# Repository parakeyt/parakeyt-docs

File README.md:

# parakeyt-docs
documentation and testing for parakeyt

# structure

## `reference-design/`
contains a completed reference design to act as a testing platform and schematic example of a potential parakeyt board.

it is hand designed, placed, and routed. it is not an actual output of the parakeyt toolchain.

# attribution
Footprints, models, symbols:
- RP2040-zero from https://github.com/crides/kleeb/ (MIT License)
- TLC59108IRGYR from manufacturer
- TLA2528IRTER from manufacturer
- AH49FNTR-G1 from manufacturer

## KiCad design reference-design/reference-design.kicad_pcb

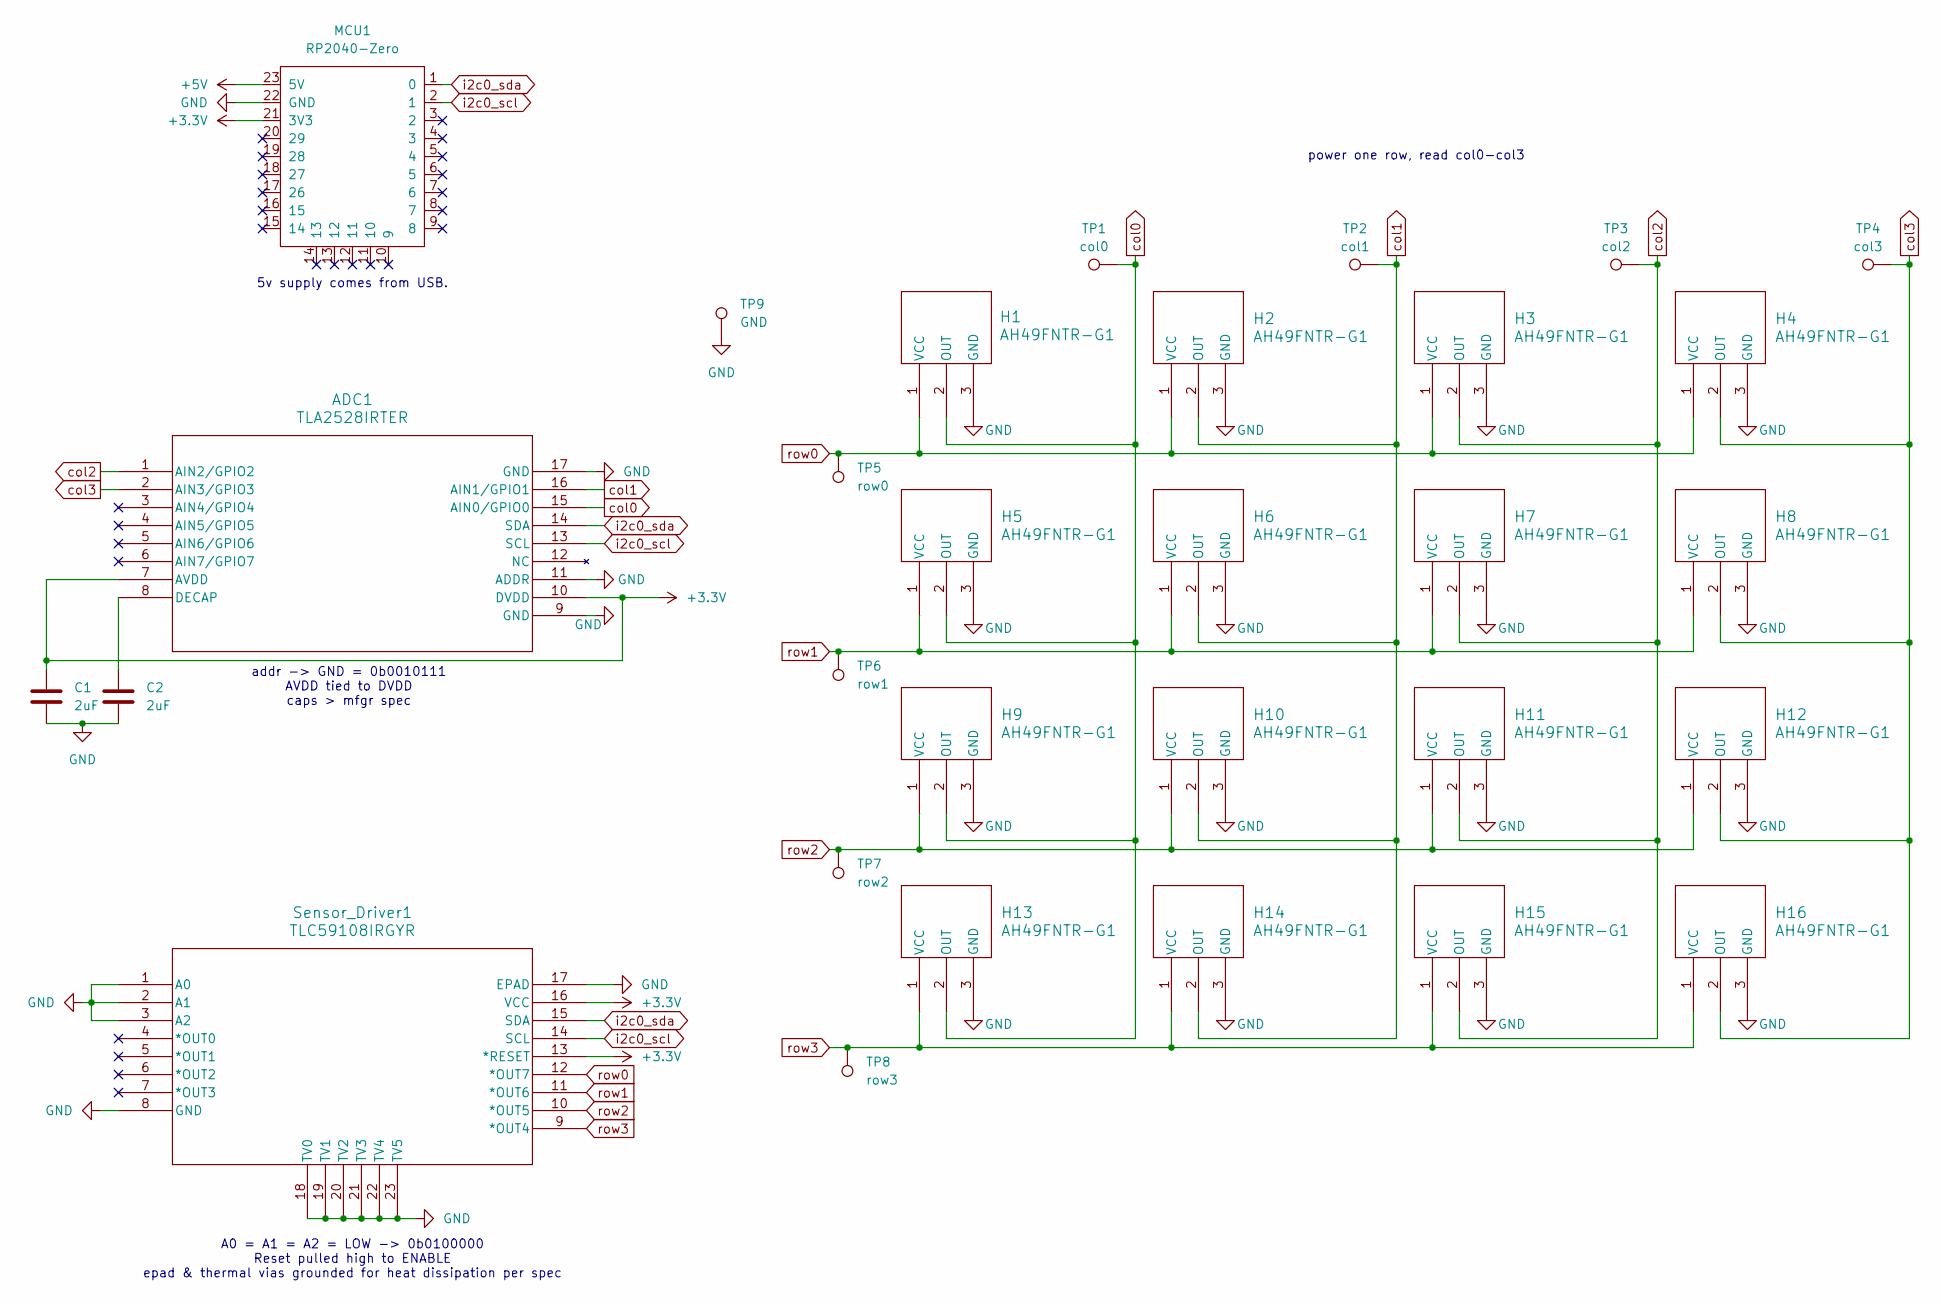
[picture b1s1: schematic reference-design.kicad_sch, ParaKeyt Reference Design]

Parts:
ADC1: TLA2528IRTER; WQFN16_RTE_TEX
C1, C2: 2uF; C_0805_2012Metric_Pad1.18x1.45mm_HandSolder
H1, H2, H3, H4, H5, H6, H7, H8, H9, H10, H11, H12, H13, H14, H15, H16: AH49FNTR-G1; SC59_DIO
MCU1: RP2040-Zero; rp2040-zero-tht
Sensor_Driver1: TLC59108IRGYR; RGY16_2P55X2P05
TP1: col0; TestPoint_Pad_2.0x2.0mm
TP2: col1; TestPoint_Pad_2.0x2.0mm
TP3: col2; TestPoint_Pad_2.0x2.0mm
TP4: col3; TestPoint_Pad_2.0x2.0mm
TP5: row0; TestPoint_Pad_2.0x2.0mm
TP6: row1; TestPoint_Pad_2.0x2.0mm
TP7: row2; TestPoint_Pad_2.0x2.0mm
TP8: row3; TestPoint_Pad_2.0x2.0mm
TP9: GND; TestPoint_Pad_2.0x2.0mm

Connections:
+3.3V: ADC1.7 (AVDD), ADC1.10 (DVDD), C1.1, MCU1.21 (3V3), Sensor_Driver1.13 (*RESET), Sensor_Driver1.16 (VCC)
+5V: MCU1.23 (5V)
GND: ADC1.9 (GND), ADC1.11 (ADDR), ADC1.17 (GND), C1.2, C2.2, H1.3 (GND), H2.3 (GND), H3.3 (GND), H4.3 (GND), H5.3 (GND), H6.3 (GND), H7.3 (GND), H8.3 (GND), H9.3 (GND), H10.3 (GND), H11.3 (GND), H12.3 (GND), H13.3 (GND), H14.3 (GND), H15.3 (GND), H16.3 (GND), MCU1.22 (GND), Sensor_Driver1.1 (A0), Sensor_Driver1.2 (A1), Sensor_Driver1.3 (A2), Sensor_Driver1.8 (GND), Sensor_Driver1.17 (EPAD), Sensor_Driver1.18 (TV0), Sensor_Driver1.19 (TV1), Sensor_Driver1.20 (TV2), Sensor_Driver1.21 (TV3), Sensor_Driver1.22 (TV4), Sensor_Driver1.23 (TV5), TP9.1
unnamed: ADC1.8 (DECAP), C2.1
col0: ADC1.15 (AIN0/GPIO0), H1.2 (OUT), H5.2 (OUT), H9.2 (OUT), H13.2 (OUT), TP1.1
col1: ADC1.16 (AIN1/GPIO1), H2.2 (OUT), H6.2 (OUT), H10.2 (OUT), H14.2 (OUT), TP2.1
col2: ADC1.1 (AIN2/GPIO2), H3.2 (OUT), H7.2 (OUT), H11.2 (OUT), H15.2 (OUT), TP3.1
col3: ADC1.2 (AIN3/GPIO3), H4.2 (OUT), H8.2 (OUT), H12.2 (OUT), H16.2 (OUT), TP4.1
i2c0_scl: ADC1.13 (SCL), MCU1.2 (1), Sensor_Driver1.14 (SCL)
i2c0_sda: ADC1.14 (SDA), MCU1.1 (0), Sensor_Driver1.15 (SDA)
row0: H1.1 (VCC), H2.1 (VCC), H3.1 (VCC), H4.1 (VCC), Sensor_Driver1.12 (*OUT7), TP5.1
row1: H5.1 (VCC), H6.1 (VCC), H7.1 (VCC), H8.1 (VCC), Sensor_Driver1.11 (*OUT6), TP6.1
row2: H9.1 (VCC), H10.1 (VCC), H11.1 (VCC), H12.1 (VCC), Sensor_Driver1.10 (*OUT5), TP7.1
row3: H13.1 (VCC), H14.1 (VCC), H15.1 (VCC), H16.1 (VCC), Sensor_Driver1.9 (*OUT4), TP8.1

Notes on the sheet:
addr -> GND = 0b0010111 AVDD tied to DVDD caps > mfgr spec
A0 = A1 = A2 = LOW -> 0b0100000 Reset pulled high to ENABLE epad & thermal vias grounded for heat dissipation per spec
5v supply comes from USB.
power one row, read col0-col3

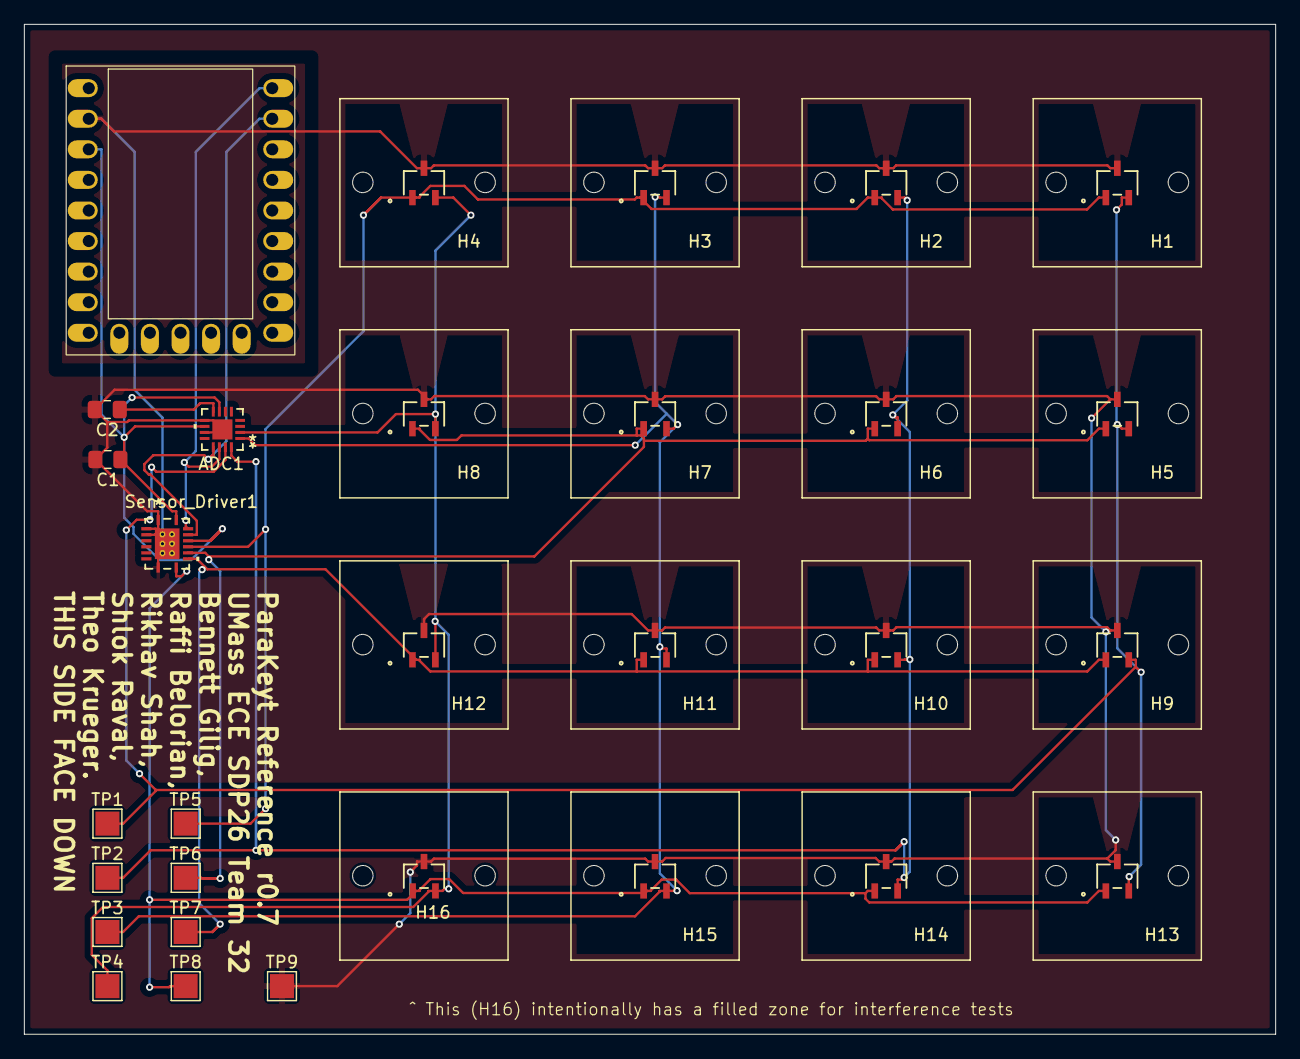
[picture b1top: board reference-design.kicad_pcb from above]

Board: 2 copper layers, 104.0 x 83.9 mm, 30 parts (0 on the bottom side), 13 nets.

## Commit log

2025-10-21 adds initial reference schematic
2025-10-22 update schematic footprints and symbols to use local for portability. fixed cap values and reset pin. re-sorted into row2col.
2025-10-22 associate 3d models for pcb preview
2025-10-22 SCH and PCB cleanup
    - Ran ERC
    - Added NCs to unused pins
    - Fixed unconnected output pin on one of the sensors
    - Cleaned up expected violations
    - Rearranged sensors on PCB to match the pattern on the schematic
2025-10-22 Edge cut issue fix
    MCU footprint had edge cuts in it for some reason which caused the 3D viewer to break. I removed the edge cuts from the footprint and the issue is now fixed.
2025-10-22 Re-commit
    Last commit had improperly saved files.
2025-10-22 fix all but 7 warnings in ERC and DRC. notably, REXT issue still needs to be resolved
2025-10-22 swap driver for non-cc version
2025-10-22 fix 3d model for slides
2025-10-23 changed MCU footprint
    Replaced throughhole MCU footprint with SMD one
2025-10-27 test autorouting, pretty cool stuff
2025-10-28 fix thermal vias
2025-10-28 add keyb outlines and rearrange grid
2025-10-29 add clearance to planes for HE sensors
2025-10-29 fix unconnected and ground plane interference problems. AAAAAAAA
2025-10-30 add testpoints
2025-11-06 create zones for interference testing
2025-11-06 Updated config.json
2025-11-06 Updated config.json mapping
2025-11-27 Update config.json
    added mcu placment
2025-11-29 fixes ADC ADDR being grounded in schematic
    PCB still not updated, needs to be re-autorouted
